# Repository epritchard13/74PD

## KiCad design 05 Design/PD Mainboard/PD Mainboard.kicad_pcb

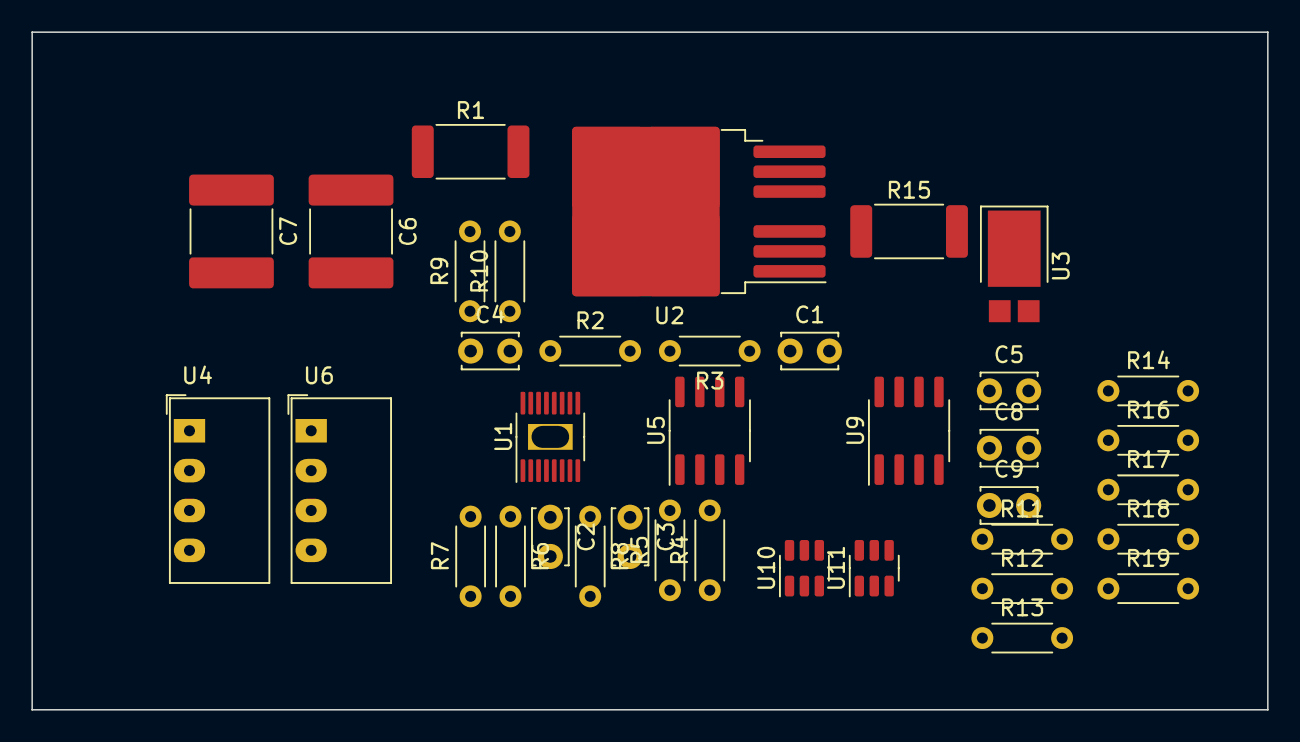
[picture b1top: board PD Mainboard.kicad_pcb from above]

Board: 2 copper layers, 78.7 x 43.2 mm, 37 parts (0 on the bottom side), 28 nets, no tracks yet.

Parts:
C1: 10000p; C_Disc_D3.4mm_W2.1mm_P2.50mm
C2, C8, C9: 1u; C_Disc_D3.4mm_W2.1mm_P2.50mm
C3, C4: 1n; C_Disc_D3.4mm_W2.1mm_P2.50mm
C5: 0.1u; C_Disc_D3.4mm_W2.1mm_P2.50mm
C6, C7: C; C_2220_5650Metric_Pad1.97x5.40mm_HandSolder
R1, R15: 0.0015; R_2512_6332Metric_Pad1.40x3.35mm_HandSolder
R2, R5, R8, R11, R13: 100k; R_Axial_DIN0204_L3.6mm_D1.6mm_P5.08mm_Horizontal
R3: 200; R_Axial_DIN0204_L3.6mm_D1.6mm_P5.08mm_Horizontal
R4, R7, R12, R14, R16, R17, R18, R19: 10k; R_Axial_DIN0204_L3.6mm_D1.6mm_P5.08mm_Horizontal
R6: 1Meg; R_Axial_DIN0204_L3.6mm_D1.6mm_P5.08mm_Horizontal
R9, R10: 10; R_Axial_DIN0204_L3.6mm_D1.6mm_P5.08mm_Horizontal
U1: MSOP-16-1EP-HOLE
U2: TO-263-6
U3: D_PowerDI-5
U4, U6: CRE1S2405SC; Converter_DCDC_Murata_CRE1xxxxxxSC_THT
U5, U9: LM358; SOIC-8_3.9x4.9mm_P1.27mm
U10, U11: MCP4725xxx-xCH; SOT-23-6

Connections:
+5V: U5.8 (V+), U6.4 (+VOUT), U9.8 (V+), U10.3 (VDD), U11.3 (VDD)
+24V: U4.2 (+VIN), U6.2 (+VIN)
-5V: U4.3 (-VOUT), U5.4 (V-), U9.4 (V-)
/Load_Switch/BOOST: C5.2, U1.14 (BST)
/Load_Switch/GATE: R2.2, R3.2, U1.11 (TGDN), U2.1
/Load_Switch/IMON: R5.2, U1.10 (IMON), U5.3 (+)
/Load_Switch/ISET: R4.2, U1.9 (ISET)
/Load_Switch/ISNS: R11.1, U5.1, U9.3 (+), U9.5 (+)
/Load_Switch/LSW_IN: C6.1, C7.1, R1.1, R6.2, R9.2, U1.2 (VIN)
/Load_Switch/LSW_OUT: R13.2, R15.2, U3.1
/Load_Switch/SNS_n: C4.2, R10.1, U1.15 (SNS_n)
/Load_Switch/SNS_p: C4.1, R9.1, U1.16 (SNS_p)
/Load_Switch/TGUP: R2.1, U1.12 (TGUP)
/Load_Switch/THRESHOLD_1: C8.1, R16.2, R19.1, U9.6 (-)
/Load_Switch/THRESHOLD_2: C9.1, R17.2, R18.1, U9.2 (-)
/Load_Switch/VSNS: U5.6 (-), U5.7
GND: C1.2, C2.2, C3.2, C6.2, C7.2, C8.2, C9.2, R4.1, R5.1, R7.1, R12.2, R14.1, R18.2, R19.2, U1.17 (EP), U3.2, U4.1 (-VIN), U4.4 (+VOUT), U6.1 (-VIN), U6.3 (-VOUT), U10.2 (VSS), U11.2 (VSS)
unnamed: C1.1, R3.1
unnamed: R1.2, R10.2, U2.4
unnamed: R8.1, U1.5 (FAULT_n)
unnamed: R6.1, R7.2, U1.1 (RUN)
unnamed: C3.1, U1.6 (TIMER)
unnamed: C5.1, R15.1, U1.13 (TS), U2.2, U2.3, U2.5, U2.6, U2.7
unnamed: C2.1, R8.2, U1.3 (VCC)
unnamed: R11.2, R12.1, U5.2 (-)
unnamed: R13.1, R14.2, U5.5 (+)
unnamed: R16.1, U10.1 (VOUT)
unnamed: R17.1, U11.1 (VOUT)

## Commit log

2026-02-02 Mainboard begin sch capture
2026-02-02 load switch with iso spi idea
